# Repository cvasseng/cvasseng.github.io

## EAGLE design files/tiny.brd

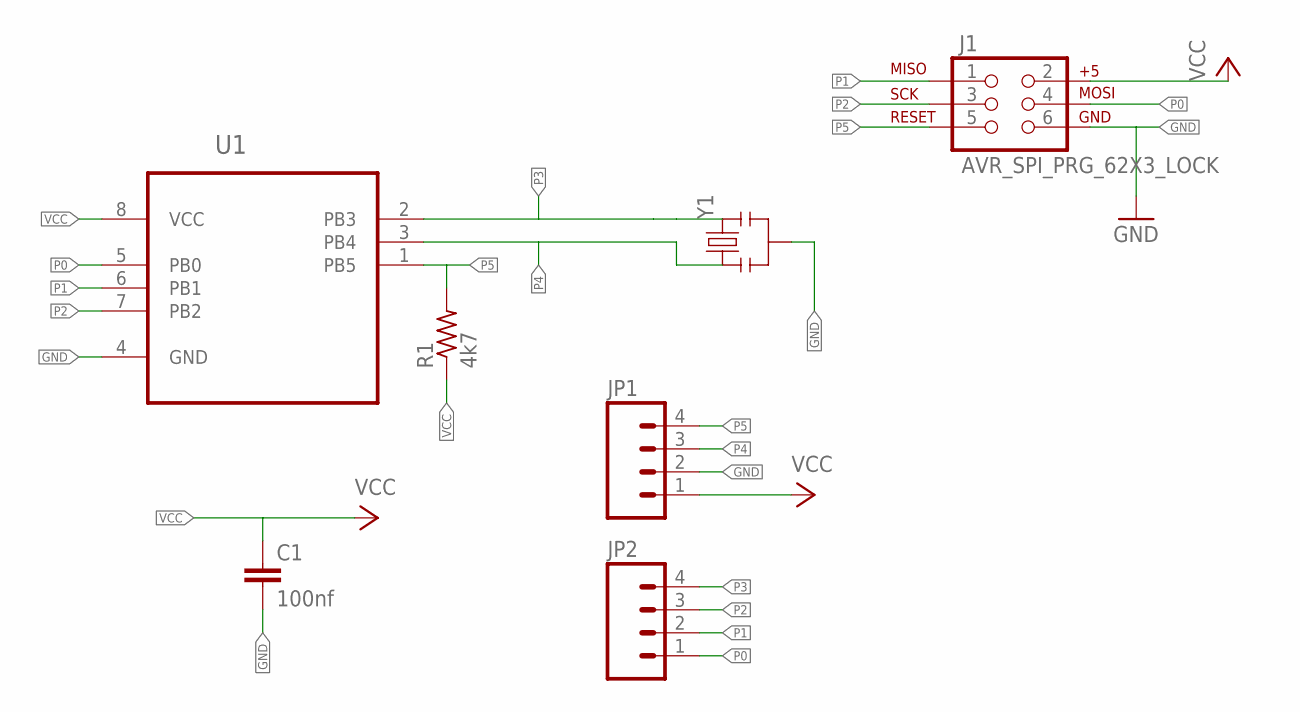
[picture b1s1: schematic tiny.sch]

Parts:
C1: 100nf; C025-024X044
J1: AVR_SPI_PRG_62X3_LOCK; 2X3_LOCK
JP1, JP2: M04LOCK; 1X04_LOCK
R1: 4k7; 0207/12
U1: ATTINY25V-10PU; DIP254P762X533-8
Y1: RESONATORPTH; RESONATOR-PTH

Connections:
GND: C1.2, J1.6, JP1.2, U1.4 (GND), Y1.2
P0: J1.4, JP2.1, U1.5 (PB0)
P1: J1.1, JP2.2, U1.6 (PB1)
P2: J1.3, JP2.3, U1.7 (PB2)
P3: JP2.4, U1.2 (PB3), Y1.3
P4: JP1.3, U1.3 (PB4), Y1.1
P5: J1.5, JP1.4, R1.2, U1.1 (PB5)
VCC: C1.1, J1.2, JP1.1, R1.1, U1.8 (VCC)

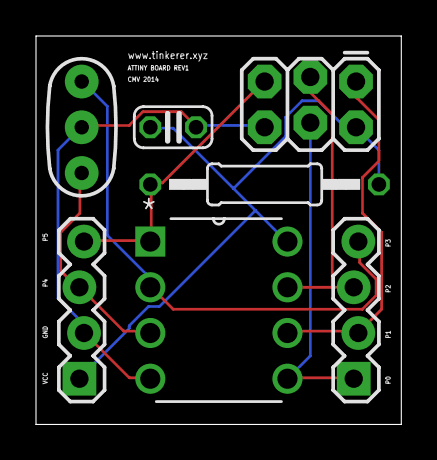
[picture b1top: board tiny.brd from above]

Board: 2 copper layers, 20.3 x 21.6 mm, 7 parts (0 on the bottom side), 8 nets.

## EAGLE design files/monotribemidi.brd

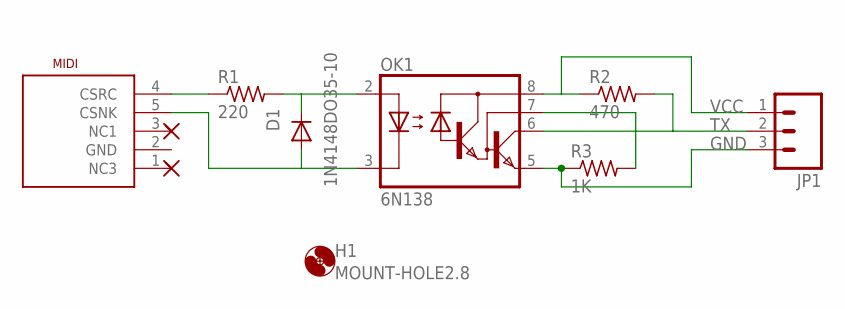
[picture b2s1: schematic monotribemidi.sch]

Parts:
D1: 1N4148DO35-10; DO35-10
H1: MOUNT-HOLE2.8; 2,8
JP1: M03LOCK; 1X03_LOCK
MIDI: MIDI_CONN_FEMALE_SUPPORT; DIN_5_FEMALE_SUPPORT
OK1: 6N138; DIL08
R1: 220; 0207/12
R2: 470; 0207/12
R3: 1K; 0207/12

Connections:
GND: JP1.3, OK1.5 (GND), R3.1
unnamed: MIDI.4 (CSRC), R1.1
unnamed: D1.C, OK1.2 (A), R1.2
unnamed: D1.A, MIDI.5 (CSNK), OK1.3 (C)
unnamed: OK1.7 (VB), R3.2
TX: JP1.2, OK1.6 (VO), R2.2
VCC: JP1.1, OK1.8 (VCC), R2.1

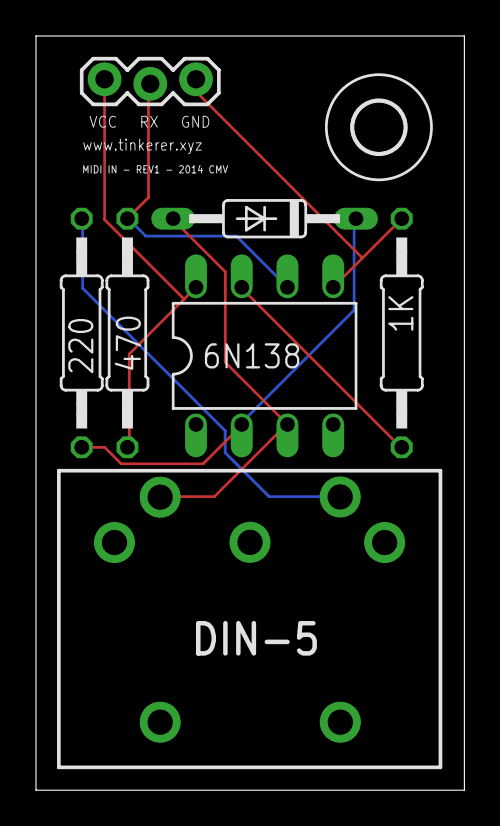
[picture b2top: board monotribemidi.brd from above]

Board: 2 copper layers, 23.8 x 41.9 mm, 8 parts (0 on the bottom side), 7 nets.

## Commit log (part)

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2016-03-06 Site updated: 2016-03-06 21:22:32
2016-03-06 Site updated: 2016-03-06 21:31:10
2016-03-06 Site updated: 2016-03-06 21:32:33
2016-03-06 flush
2016-03-06 Playlets version of magescape
2016-03-06 Fixe fixe
2019-07-08 Added pubkey
2019-07-10 Update CNAME
2019-07-10 Flushed homepage
2026-05-18 Added midi -> stem tool
2026-05-18 Bugfixing

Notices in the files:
parts and their libraries:
SparkFun-Connectors: Licensing: Creative Commons ShareAlike 4.0 International - https://creativecommons.org/licenses/by-sa/4.0
